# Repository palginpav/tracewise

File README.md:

# TraceWise

**AI-assisted place & route for KiCad** — schematic review with datasheet grounding, constraint
generation for autorouting, and analytical placement. Open source, local-first.

> Status: **v0.2** — Reviewer + constraint generation + a battle-tested Freerouting bridge.
> `review` scores **1.00 recall / 1.00 precision** on the seeded benchmark
> ([scorecards](docs/review-benchmark.md)). `constrain` + `route` work end-to-end on real
> community boards — outline healing, ref sanitization and DSN-incompatibility auto-bisect
> included, because real boards needed all of it. Routing ablation on three open-hardware
> boards: **mixed, honestly analyzed** ([results](docs/route-ablation-v2.md)) — constraints
> helped the dense 2-layer, hurt the tight 4-layer, and Freerouting's own ceiling dominates.
> Design: [docs/DESIGN.md](docs/DESIGN.md) · roadmap: [docs/PLAN.md](docs/PLAN.md) ·
> why not kiutils: [docs/spike-0-kiutils.md](docs/spike-0-kiutils.md)

## The idea

Autorouters disappoint not because the solvers are weak, but because nobody feeds them the
constraints that make routing meaningful — net classes, differential pairs, length rules, fanout
strategy. Schematic review tools check syntax, not electronics. TraceWise applies LLMs exactly
where they help:

- **Reviewer** — reads your netlist, cross-checks parts against their datasheets (RAG), and flags
  real mistakes: missing decoupling, absent pull-ups, floating enables, off-datasheet pin usage —
  every finding cited to the datasheet
- **Fixer** — proposes mechanical corrections as reviewable patches to your schematic; you approve
  each one, nothing is ever edited silently
- **Placer** — analytical (gradient-descent) placement with electronics-aware cost terms:
  decoupling proximity, thermal spread, functional-block cohesion
- **Router** — generates formal constraints (`.kicad_dru`, Specctra rules) from netlist semantics
  and your stack-up, drives Freerouting through the proven DSN/SES bridge, and iterates against DRC

**What TraceWise does not pretend:** no autorouter in 2026 — commercial or otherwise — produces
sign-off-grade routing for high-speed designs, and neither does this. TraceWise makes the boring
80% disappear and shows its work on the rest. Signal-integrity judgment stays with you.

## Honest scope

Targets DRC-clean results on ~2–4 layer, sub-50 MHz-class digital and mixed-signal boards.
High-speed designs get constraint *suggestions*, not autonomous routing. Findings ship with
datasheet citations; metrics ship with every release (seeded-error benchmarks for the Reviewer,
constrained-vs-naked Freerouting ablations for the Router).

## Architecture (short)

A standalone Python engine (CLI-first) + a thin KiCad plugin (PCM). Schematic access via
`kicad-cli` + file-level parsing (KiCad has no live schematic API); board operations via the
official IPC API; routing via the Freerouting DSN/SES bridge; LLM runs locally (Ollama) with an
optional hosted-API mode. Details and platform constraints: [docs/DESIGN.md](docs/DESIGN.md).

## License

[Apache-2.0](LICENSE). KiCad demo files used in tests are fetched, not redistributed.

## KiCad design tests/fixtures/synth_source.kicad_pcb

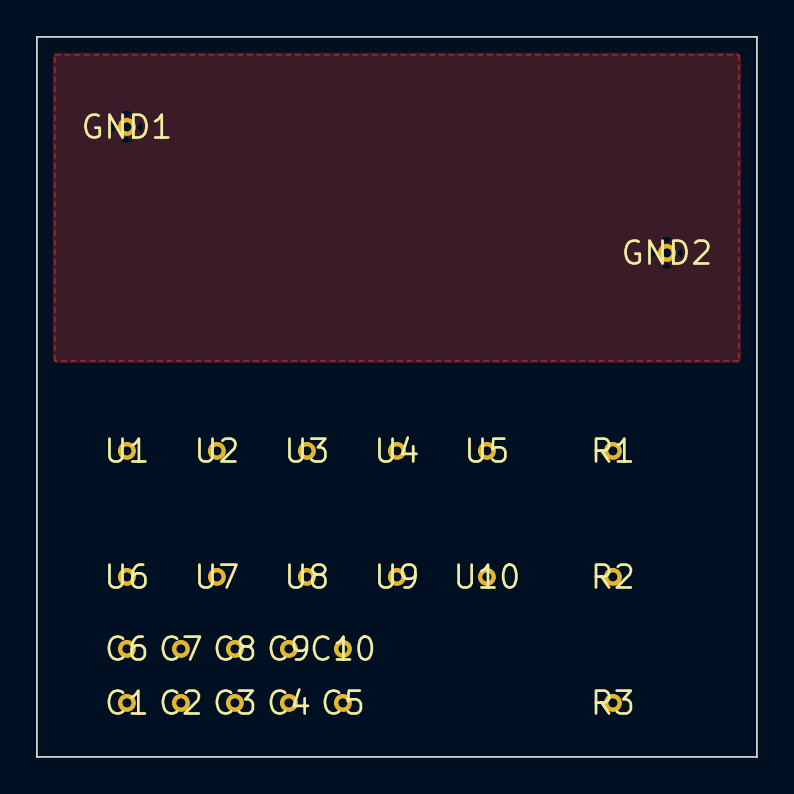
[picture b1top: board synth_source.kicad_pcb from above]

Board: 2 copper layers, 40.0 x 40.0 mm, 25 parts (0 on the bottom side), 4 nets, no tracks yet.

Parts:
C1, C2, C3, C4, C5, C6, C7, C8, C9, C10: (no value)
GND1, GND2: (no value)
R1, R2, R3: (no value)
U1, U2, U3, U4, U5, U6, U7, U8, U9, U10: (no value)

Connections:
+3V3: R1.1, R2.1, R3.1
+5V: U1.1, U2.1, U3.1, U4.1, U5.1, U6.1, U7.1, U8.1, U9.1, U10.1
GND: GND1.1, GND2.1
SIG: C1.1, C2.1, C3.1, C4.1, C5.1, C6.1, C7.1, C8.1, C9.1, C10.1

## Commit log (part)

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2026-06-11 init: scaffold + spike 0 — kiutils is a no-go
    Design (docs/DESIGN.md), roadmap (docs/PLAN.md), and the first
    de-risking spike: kiutils round-trips 0/9 official KiCad demo files
    cleanly (v9 and v10) — board files crash or corrupt, schematics
    silently lose 8-17% of tokens. Decision: build a small lossless
    s-expression editor instead; the spike harness becomes its regression
    suite. Full report in docs/spike-0-kiutils.md.
2026-06-11 docs: v0.1 status in README
2026-06-11 fix: space-free intermediate filenames (Freerouting launcher splits on spaces)
2026-06-11 docs: designer review of ablation boards — router is the bottleneck, roadmap updated
2026-06-11 feat: router R0 — occupancy grid + A* + path simplification
    The engine's foundation per docs/ROUTER-DESIGN.md: clearance-inflated
    occupancy grid (free cell = legal centerline by construction), 8-dir
    A* with via moves and multi-goal search (connection-tree growth),
    explicit failure with no partial path (dangling stubs inexpressible),
    collinear/45° simplification split at vias.
    Fun test moment: the obstacle-detour test failed because the router
2026-06-11 feat: router clearance tuning — four measured hypotheses, two confirmed
    Forensics on the 68-violation clearance class, instance by instance:
    (1) via inflation omitted the approaching track's halfwidth — the
    repeating 0.125mm-actual class, now geometrically impossible;
    (2) via placement gets a 2-cell free ring on both layers (barrel copper
    outsticks the track halfwidth the grid budgets);
    (3) no-corner-cutting: 45-degree segments between free cells still clip
2026-06-11 feat: tracewise auto — sequential refinement loop toward 0/0
    Operator-designed iteration: each round feeds failures back (failed
    nets route first next round, rip-up budget escalates), every round
    restarts from the pristine board, only improvements stick.
    First measurement says the quiet part: ordering feedback alone is
    zero-sum on a dense board — routed nets rose 35->40 across rounds while
    pad-level unconnected churned 63->64-69 (rollback kept 63). Corridors
2026-06-12 ECCF gates on mitayi: V1 pass 100%, V2 inconclusive (harness saturates)
    V1: 41/41 parts recover human orientation in top-2. V2 rho=0.452 but
    14/18 deltas were exactly 0.0 (T2 window seals without escape-allowance
    modeling — the documented limit). Fix window passability, re-run.
    Also: deterministic engine crash repro found at trial 16.
2026-06-12 docs: dev-machine CPU core degradation note (taskset workaround)
2026-06-13 docs: layer-aware placer shipped; flag dense-board route perf cliff
    A zuluscsi via-sweep route hung 21min at full CPU on via_cost=10 — the
    router needs a hard per-net expansion/time cap so a pathological route
    fails explicitly instead of hanging the loop. Queued, with the
    build-order progress and the via-cost-negative note.
2026-06-14 auto loop: explore from stripped placement + combined keep-best score
    Two coupled fixes the mitayi validation exposed. (1) The exploration
    base must be a STRIPPED placement: re-routing the previous routed board
    piled copper on copper (errors 82->990). Now each iter routes a clean
    placement and only the winning stripped placement carries forward.
    (2) keep-best uses unconnected*5 + errors, not lexicographic — which
    had accepted 49/655 over 56/88. T3 trial-reset also restores to the
2026-06-14 docs: zuluscsi is routing-QUALITY-bound, not speed/timeout-bound
    1800s budget routes more (unc 48->27, time-bound confirmed) but errors
    balloon 105->290 (combined score worse): the router forces connections
    through clearance violations. Coarser pitch worse too. The wall is
    routing quality (escape-shaving over legal paths), not speed. Next:
    legality-first routing.
2026-06-17 Add PathFinder negotiated-congestion router
    Prices grid contention instead of forbidding it: a committed track inflates
    an occ plane (halfwidth+clearance), and over-used nets rip up and reroute at a
    rising congestion price until no halo cell is shared. Halo-aware pricing
    (dilate occ by halfwidth before reading cost) so footprint overlaps are
    penalised, not just centerline collisions.
2026-06-17 Vectorize A* heuristic: 62% of route time was the goal-loop
    The octile heuristic looped over every goal cell per node expansion; since
    goals is the whole growing connection tree, profiling showed h() at 62% of
    route time (1.6B min/abs calls). Keep it exact (A* stays optimal) but vectorize
    with numpy for large goal sets. mitayi 290s->196s (-32%), routed 35->39 (routes
    that used to hit the 45s wall-clock cap now finish), unconnected held at 63.
2026-06-17 Phase 0: F0 pour-extraction design + F3 high-fanout-power survey
    F0: extract pour geometry + unconnected pads via pcbnew API (not fragile s-expr);
    net-agnostic, reused by F2/F3. F3 survey verdict: synthesize a lower-priority +3V0
    zone and reuse F2 stub-stitch -- integration, not a new algorithm.
2026-06-18 PLAN: session summary (router speedups + pour-completion arc)
2026-06-18 Clean up place_route_measure.py lint (no semicolons/compound stmts)
2026-06-18 Multi-board confirmation: all originals 2-layer human-routed (~0 unconn); ceiling claims superseded
    mitayi human 0/0, zuluscsi 0/5, rp2040 3/65 -- all 2-layer. Our 63/65/84 is pure router
    quality. Success metric corrected to: match the human (0 unconnected on 2 layers). The real
    open problem is high-fanout trace routing with persistence (route hard nets with detours+vias,
    don't abandon them), not layers.
2026-06-18 Diagnose mitayi persistence: congestion/order not intrinsic (+3V3 routes alone; order helps 48->43 zero-sum; GND trace tree redundant+harmful)
2026-06-18 Phase 1 architecture + probe revision: coarse grid must be capacity-based (boolean is degenerate)
    Authored PHASE1-coarsen-refine-architecture.md (coarse negotiate -> corridor refine -> salvage,
    all on existing parts). Probe of the central assumption found the naive coarse grid
    (build_problem at 0.2mm) is DEGENERATE for fine-pitch boards (ok=0/61, 583s) -- the fine
    clearance inflation exceeds the coarse pitch. Revision: Stage-1 coarse grid must be a
    CAPACITY-based global-routing graph (FPGA-style, tracks-per-cell), not boolean. Deeper: mitayi
    is human-routable yet our grid can't find it -> 0.1mm quantization over-estimates congestion ->
2026-06-18 probes: #4 nudgeability analysis + clean human-placement route helper
    probe_clearance_nudgeability.py — numpy exact segment/via-to-copper distance
    analysis that classified mitayi's 74 clearance-class errors (endpoint-nudgeable
    vs mid-segment vs pour-interaction) to set the #4 ceiling (PROBE-A: 0
    pour-interaction; pad<->track the cleanly-addressable class).
    _probe_route_human.py — routes a board's HUMAN placement clean (strip + route
    + DRC), mirroring place_route_measure step 1, so probes measure against the
2026-06-19 FAR gridless: M1 scale-spike run-1 NO-GO (fixable) + own-pad carve-out design gap
    Record the M1 scale-spike findings: 3/4 failures were spike defects (double-
    inflation legality check, determinism harness contamination, wrong region for
    connectivity), 1 was a real substrate gap — the gridless free-space build must
    carve the routing net's OWN pad rects out of accumulated obstacles (mirroring
    build_problem's carve), now a documented substrate requirement. Recalibrate the
    M1 scale spike to validate legality+runtime+determinism only; connectivity-relief
2026-06-19 FAR gridless M2: optimize visibility-graph runtime 7.94x -> 2.69x grid
    Option (b) — make the M2 congestion+rip-up mechanism fast without changing
    results or the substrate. Vectorized the hot edge-build in the PRODUCTION
    search.py build_visibility_graph (M1 benefits too):
    - vectorized shapely.contains_xy midpoint pre-filter (was per-point Point() creates);
    - single batched STRtree.query over all candidate edges (was O(n²) per-edge queries).
    M2 spike runtime now 2.69x grid --quality (<=3x target MET). ALL invariants
2026-06-20 FAR gridless M3-P1.1: gridless-first tested — opposite failure mode (slow)
    Wire geometry-blocked nets to attempt 2-layer in the gridless-FIRST negotiate
    path (multi.py: _route_net_2layer on geometry_blocked before grid claims
    corridors; bounded via-search window). No-op-safe (gridless_negotiate=False
    byte-identical), suite green, ruff clean.
    Decisive finding: gridless-first is PATHOLOGICALLY SLOW — even 2 QSPI nets
    (/QSPI_SCLK,/QSPI_SD2) didn't finish routing in >25min. Root cause: clean-board
2026-06-21 FAR gridless: gridless-first param scaffolding (PARTIAL — perf path missing)
    Wire gridless_first: set[str]|None into route_all/route_board_engine: no-op-safe
    (gridless_first=None byte-identical, suite green, ruff check . clean). Adds
    test_gridless_first.py + the A/B harness scripts/_verify_gridless_first_ab.py.
    HONEST: this is PARTIAL and the connectivity gate is UNMEASURED. gridless_first
    merely activates the existing gridless_negotiate path (merge set, force
    negotiate=True) — it does NOT implement Probe-Order's perf-critical fast path
2026-06-22 FAR: fanout-escape production — mechanism scales (10/17) but net regression vs attempt-3
    Built QFN fanout-escape into the gridless-first path: dense-component detection,
    guided escape-via placement (ray from component centroid through source pad, just
    outside the pad ring, bounded), all_rings corner mode (dense-pad source pads),
    F.Cu-stub + B.Cu-run per net. gridless_first=None byte-identical; 392 tests green;
    ruff clean; deterministic; fast (94s).
    PM-verified A/B (the building agent's "GATE MET" was vs the WRONG baseline):
2026-06-23 FAR: two inventor proposals — gap is ORDERING/homotopy, not capacity
    Two opus/max inventors studied the human's 0/0 witness board and CONVERGED:
    INVENT-1 (human-mimicry): the human assigns a GLOBAL TOPOLOGY first — escape-ring
    via-slot (39 vias, balanced 4.55-8.18mm band) + layer=direction (B.Cu 67%
    horizontal highways, F.Cu 80% vertical) + monotone B.Cu bus (crossing-free
    river-routing). Invented topology-first router: phase-1 combinatorial slot/lane
    packing (collisions PREVENTED by disjoint packing), phase-2 realize on existing
